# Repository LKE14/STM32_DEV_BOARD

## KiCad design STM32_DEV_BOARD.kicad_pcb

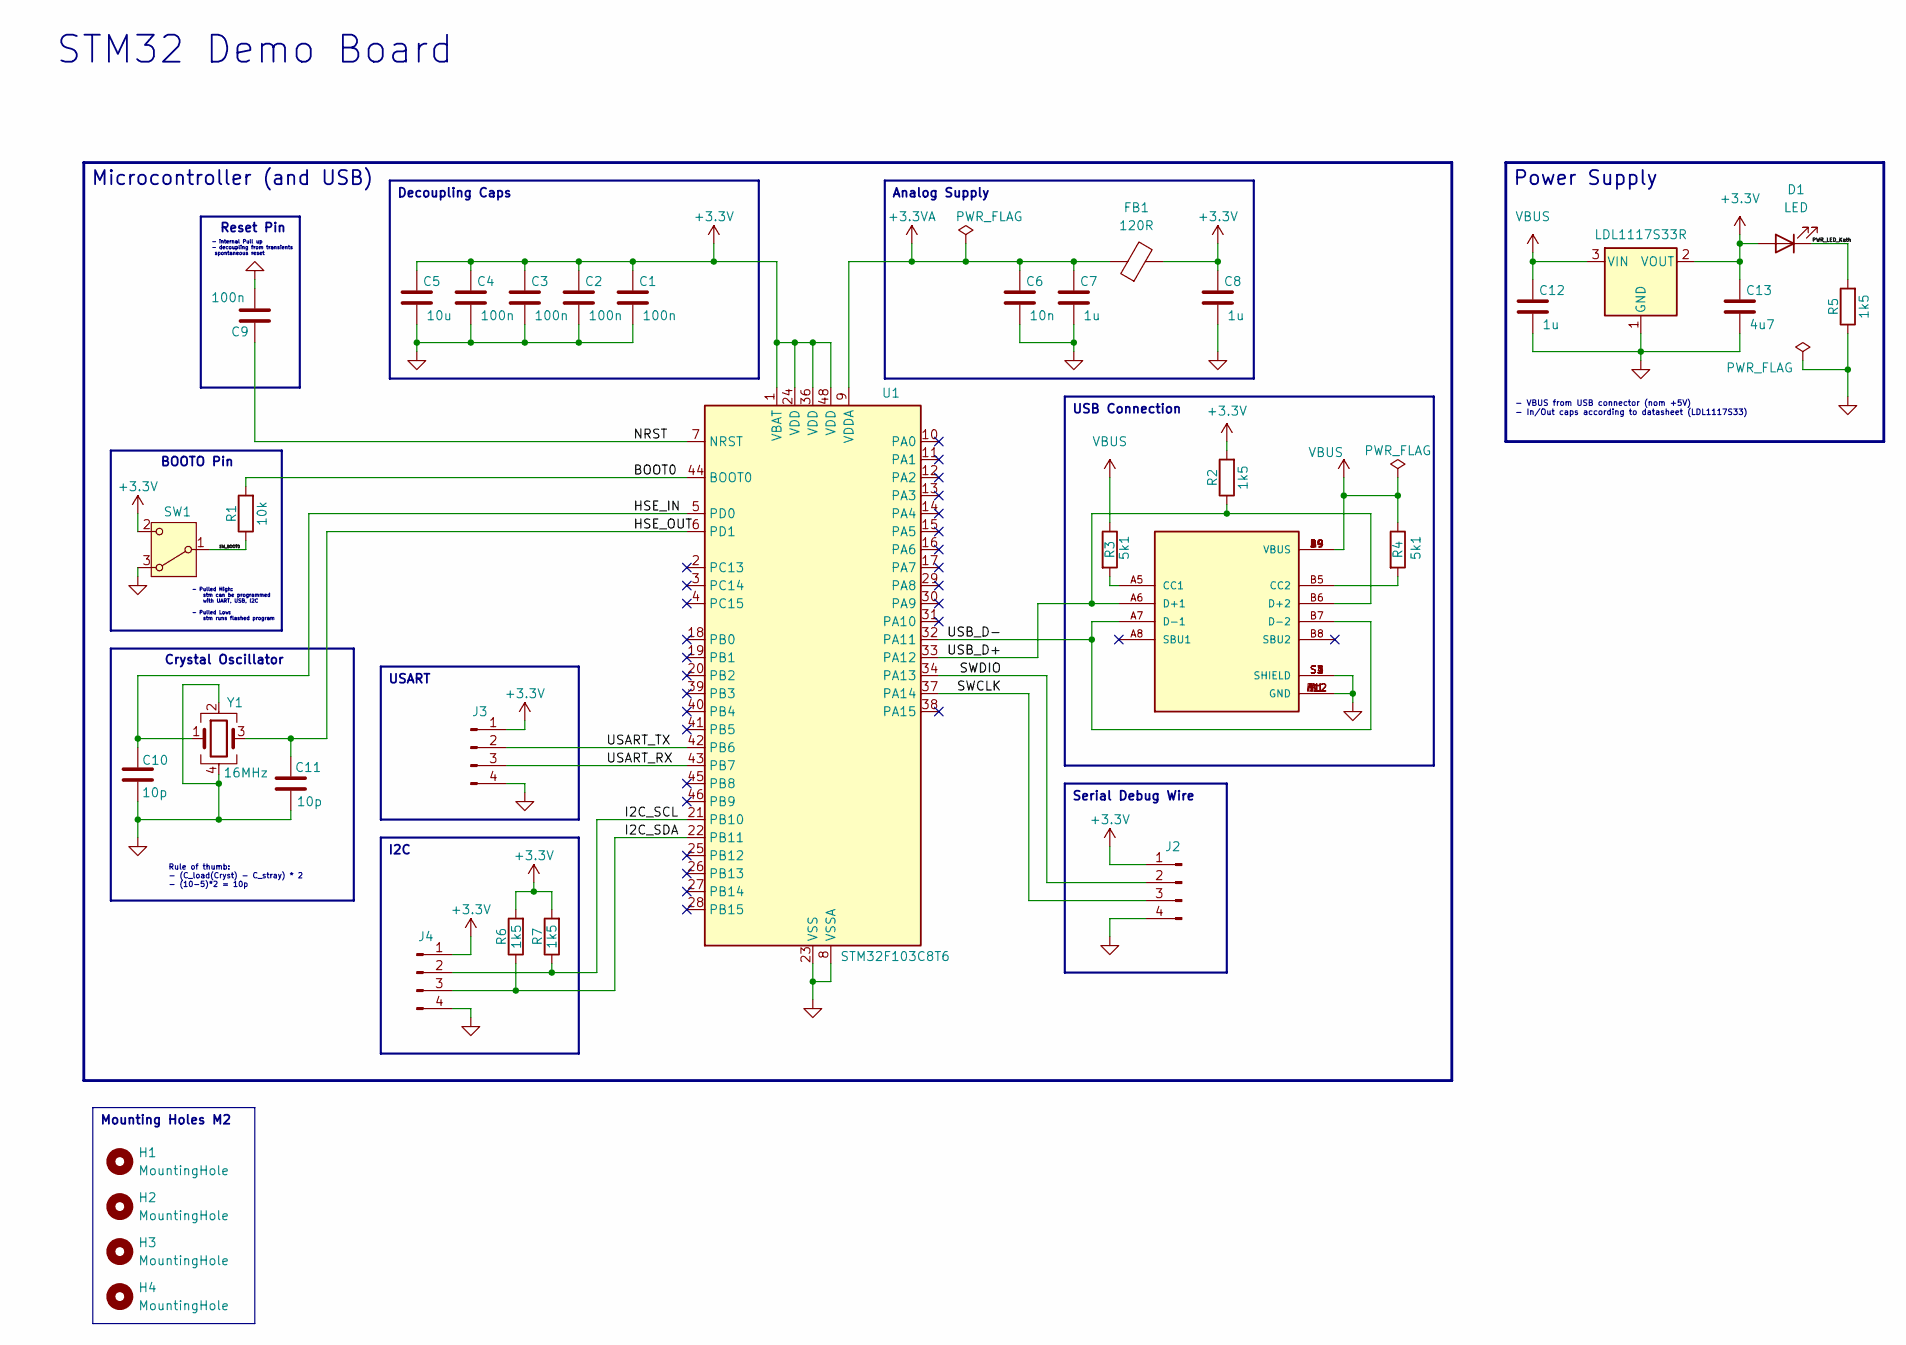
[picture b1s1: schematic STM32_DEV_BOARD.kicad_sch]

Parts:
C1, C2, C3, C4, C9: 100n; C_0603_1608Metric_Pad1.08x0.95mm_HandSolder
C5: 10u; C_0603_1608Metric_Pad1.08x0.95mm_HandSolder
C6: 10n; C_0603_1608Metric_Pad1.08x0.95mm_HandSolder
C7, C8, C12: 1u; C_0603_1608Metric_Pad1.08x0.95mm_HandSolder
C10, C11: 10p; C_0603_1608Metric_Pad1.08x0.95mm_HandSolder
C13: 4u7; C_0603_1608Metric_Pad1.08x0.95mm_HandSolder
D1: LED; LED_0805_2012Metric_Pad1.15x1.40mm_HandSolder
FB1: 120R; L_0805_2012Metric_Pad1.15x1.40mm_HandSolder
H1, H2, H3, H4: MountingHole; MountingHole_2.2mm_M2
J2, J3, J4: Conn_01x04_Pin; PinHeader_1x04_P2.54mm_Vertical
J5: 629722000214; WURTH_629722000214; PARTREV 001.001
R1: 10k; R_0805_2012Metric_Pad1.20x1.40mm_HandSolder
R2, R5, R6, R7: 1k5; R_0805_2012Metric_Pad1.20x1.40mm_HandSolder
R3, R4: 5k1; R_0805_2012Metric_Pad1.20x1.40mm_HandSolder
SW1: SW_Wuerth_450301014042; SW_Slide-03_Wuerth-WS-SLTV_10x2.5x6.4_P2.54mm
U1: STM32F103C8T6; LQFP-48_7x7mm_P0.5mm
U3: LDL1117S33R; SOT-223-3_TabPin2
Y1: 16MHz; Crystal_SMD_3225-4Pin_3.2x2.5mm

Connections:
+3.3V: C1.1, C2.1, C3.1, C4.1, C5.1, C8.1, C13.1, D1.2 (A), FB1.2, J2.1, J3.1, J4.1, R2.2, R6.2, R7.2, SW1.2 (C), U1.1 (VBAT), U1.24 (VDD), U1.36 (VDD), U1.48 (VDD), U3.2 (VOUT)
+3.3VA: C6.1, C7.1, FB1.1, U1.9 (VDDA)
/BOOT0: R1.2, U1.44 (BOOT0)
/HSE_IN: C10.1, U1.5 (PD0), Y1.1
/HSE_OUT: C11.1, U1.6 (PD1), Y1.3
/I2C_SCL: J4.2, R7.1, U1.21 (PB10)
/I2C_SDA: J4.3, R6.1, U1.22 (PB11)
/NRST: C9.1, U1.7 (NRST)
/PWR_LED_Kath: D1.1 (K), R5.2
/SWCLK: J2.3, U1.37 (PA14)
/SWDIO: J2.2, U1.34 (PA13)
/SW_BOOT0: R1.1, SW1.1 (B)
/USART_RX: J3.3, U1.43 (PB7)
/USART_TX: J3.2, U1.42 (PB6)
/USB_D+: J5.A6 (D+1), J5.B6 (D+2), R2.1, U1.33 (PA12)
/USB_D-: J5.A7 (D-1), J5.B7 (D-2), U1.32 (PA11)
GND: C1.2, C2.2, C3.2, C4.2, C5.2, C6.2, C7.2, C8.2, C9.2, C10.2, C11.2, C12.2, C13.2, J2.4, J3.4, J4.4, J5.A1 (GND), J5.A12 (GND), J5.B1 (GND), J5.B12 (GND), J5.S1 (SHIELD), J5.S2 (SHIELD), J5.S3 (SHIELD), J5.S4 (SHIELD), R5.1, SW1.3 (A), U1.8 (VSSA), U1.23 (VSS), U1.35 (VSS), U1.47 (VSS), U3.1 (GND), Y1.2, Y1.4
unnamed: J5.A5 (CC1), R3.2
unnamed: J5.B5 (CC2), R4.2
VBUS: C12.1, J5.A4 (VBUS), J5.A9 (VBUS), J5.B4 (VBUS), J5.B9 (VBUS), R3.1, R4.1, U3.3 (VIN)

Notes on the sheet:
- Pulled High: stm can be programmed with UART, USB, I2C - Pulled Low: stm runs flashed program
Rule of thumb: - (C_load(Cryst) - C_stray) * 2 - (10-5)*2 = 10p
- VBUS from USB connector (nom +5V) - In/Out caps according to datasheet (LDL1117S33)
STM32 Demo Board
Reset Pin
- internal Pull up - decoupling from transients spontaneous reset
BOOTO Pin
Crystal Oscillator
USART
Power Supply
I2C
USB Connection
Microcontroller (and USB)
Serial Debug Wire
Analog Supply
Decoupling Caps
Mounting Holes M2

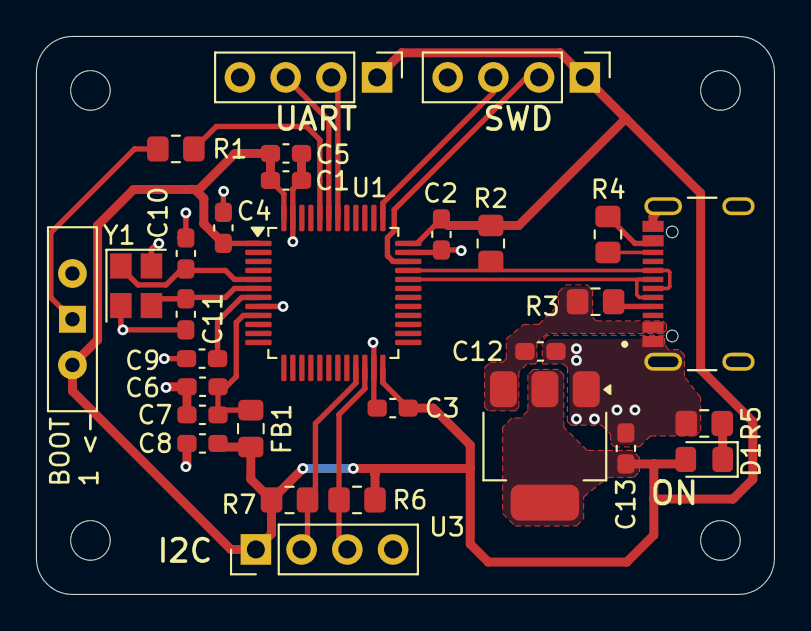
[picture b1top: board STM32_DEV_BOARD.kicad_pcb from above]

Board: 2 copper layers, 41.0 x 31.0 mm, 34 parts (0 on the bottom side), 20 nets.

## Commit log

2025-04-03 add content
2025-04-03 Schematic ready
2025-04-03 Schematic footprints asignment
2025-04-04 complete layout
2025-04-04 ready for takeoff
